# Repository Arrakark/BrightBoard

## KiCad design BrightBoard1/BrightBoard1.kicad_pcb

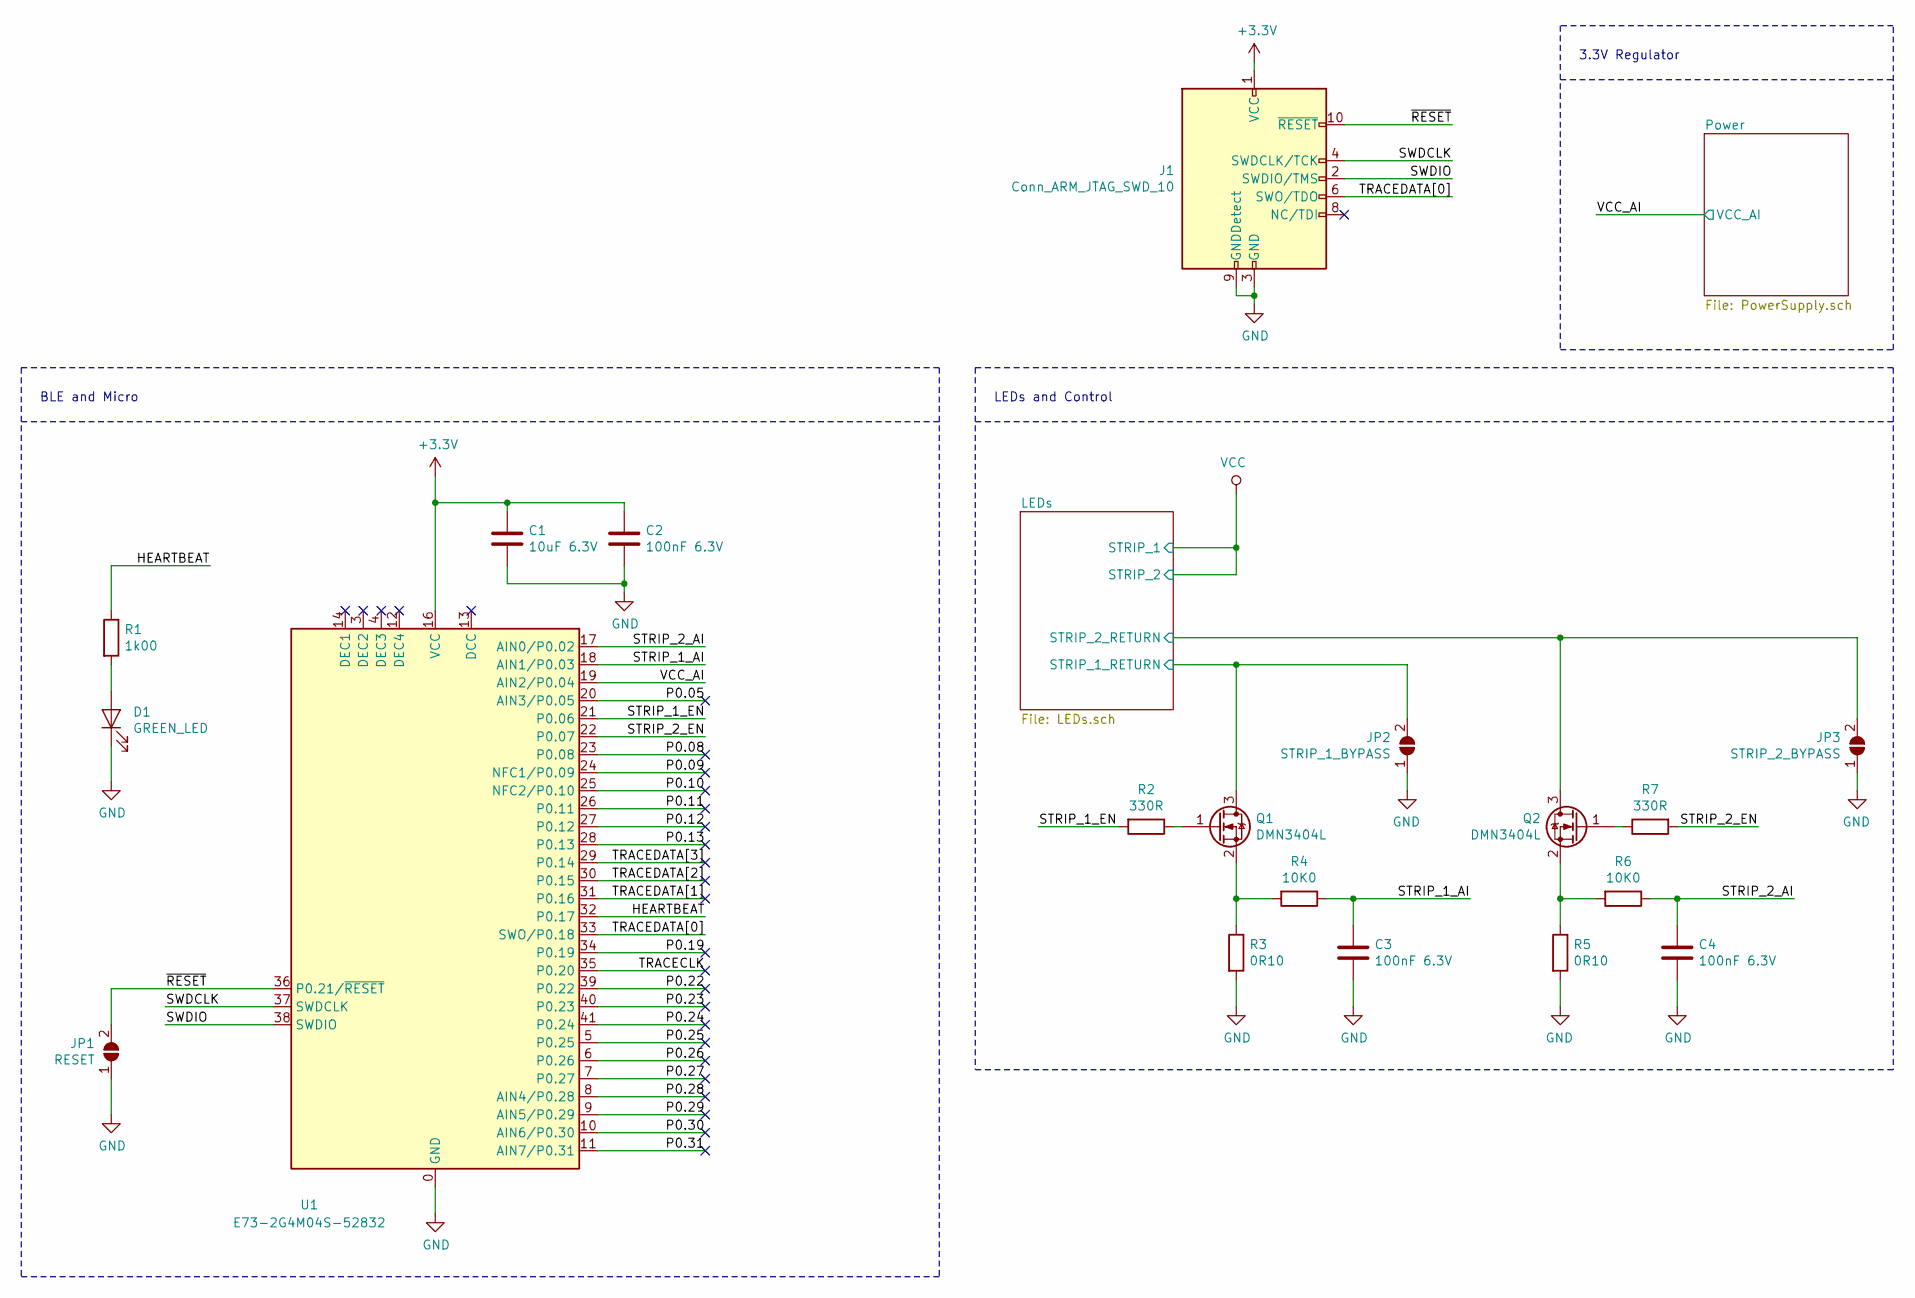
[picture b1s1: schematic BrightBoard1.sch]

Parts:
C1: 10uF 6.3V; C_0805_2012Metric_Pad1.15x1.40mm_HandSolder
C2, C3, C4: 100nF 6.3V; C_0805_2012Metric_Pad1.15x1.40mm_HandSolder
D1: GREEN_LED; LED_0805_2012Metric_Pad1.15x1.40mm_HandSolder
J1: Conn_ARM_JTAG_SWD_10; PinHeader_2x05_P1.27mm_Vertical_SMD
JP1: RESET; SolderJumper-2_P1.3mm_Open_RoundedPad1.0x1.5mm
JP2: STRIP_1_BYPASS; SolderJumper-2_P1.3mm_Open_RoundedPad1.0x1.5mm
JP3: STRIP_2_BYPASS; SolderJumper-2_P1.3mm_Open_RoundedPad1.0x1.5mm
Q1, Q2: DMN3404L; SOT-23
R1: 1k00; R_0805_2012Metric_Pad1.15x1.40mm_HandSolder
R2, R7: 330R; R_0805_2012Metric_Pad1.15x1.40mm_HandSolder
R3, R5: 0R10; R_0805_2012Metric_Pad1.15x1.40mm_HandSolder
R4, R6: 10K0; R_0805_2012Metric_Pad1.15x1.40mm_HandSolder
U1: E73-2G4M04S-52832; E73-2G4M04S

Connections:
+3V3: C1.1, C2.1, J1.1 (VCC), U1.16 (VCC); also elsewhere on the board
/HEARTBEAT: R1.1, U1.32 (P0.17)
/LEDs/STRIP_1_RETURN: JP2.2 (B), Q1.3 (D); also elsewhere on the board
/LEDs/STRIP_2_RETURN: JP3.2 (B), Q2.3 (D); also elsewhere on the board
/P0.05: U1.20 (AIN3/P0.05)
/P0.08: U1.23 (P0.08)
/P0.09: U1.24 (NFC1/P0.09)
/P0.10: U1.25 (NFC2/P0.10)
/P0.11: U1.26 (P0.11)
/P0.12: U1.27 (P0.12)
/P0.13: U1.28 (P0.13)
/P0.19: U1.34 (P0.19)
/P0.22: U1.39 (P0.22)
/P0.23: U1.40 (P0.23)
/P0.24: U1.41 (P0.24)
/P0.25: U1.5 (P0.25)
/P0.26: U1.6 (P0.26)
/P0.27: U1.7 (P0.27)
/P0.28: U1.8 (AIN4/P0.28)
/P0.29: U1.9 (AIN5/P0.29)
/P0.30: U1.10 (AIN6/P0.30)
/P0.31: U1.11 (AIN7/P0.31)
/STRIP_1_AI: C3.1, R4.1, U1.18 (AIN1/P0.03)
/STRIP_1_EN: R2.2, U1.21 (P0.06)
/STRIP_2_AI: C4.1, R6.1, U1.17 (AIN0/P0.02)
/STRIP_2_EN: R7.2, U1.22 (P0.07)
/SWDCLK: J1.4 (SWDCLK/TCK), U1.37 (SWDCLK)
/SWDIO: J1.2 (SWDIO/TMS), U1.38 (SWDIO)
/TRACECLK: U1.35 (P0.20)
/TRACEDATA[0]: J1.6 (SWO/TDO), U1.33 (SWO/P0.18)
/TRACEDATA[1]: U1.31 (P0.16)
/TRACEDATA[2]: U1.30 (P0.15)
/TRACEDATA[3]: U1.29 (P0.14)
/VCC_AI: U1.19 (AIN2/P0.04); also elsewhere on the board
/~RESET: J1.10 (~RESET~), JP1.2 (B), U1.36 (P0.21/~RESET)
GND: C1.2, C2.2, C3.2, C4.2, D1.1 (K), J1.3 (GND), J1.5 (GND), J1.9 (GNDDetect), JP1.1 (A), JP2.1 (A), JP3.1 (A), R3.2, R5.2, U1.0 (GND), U1.1 (GND), U1.2 (GND), U1.15 (GND), U1.42 (GND), U1.43 (GND); also elsewhere on the board
unnamed: D1.2 (A), R1.2
unnamed: Q1.1 (G), R2.1
unnamed: Q1.2 (S), R3.1, R4.2
unnamed: Q2.1 (G), R7.1
unnamed: Q2.2 (S), R5.1, R6.2

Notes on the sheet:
LEDs and Control
3.3V Regulator
BLE and Micro

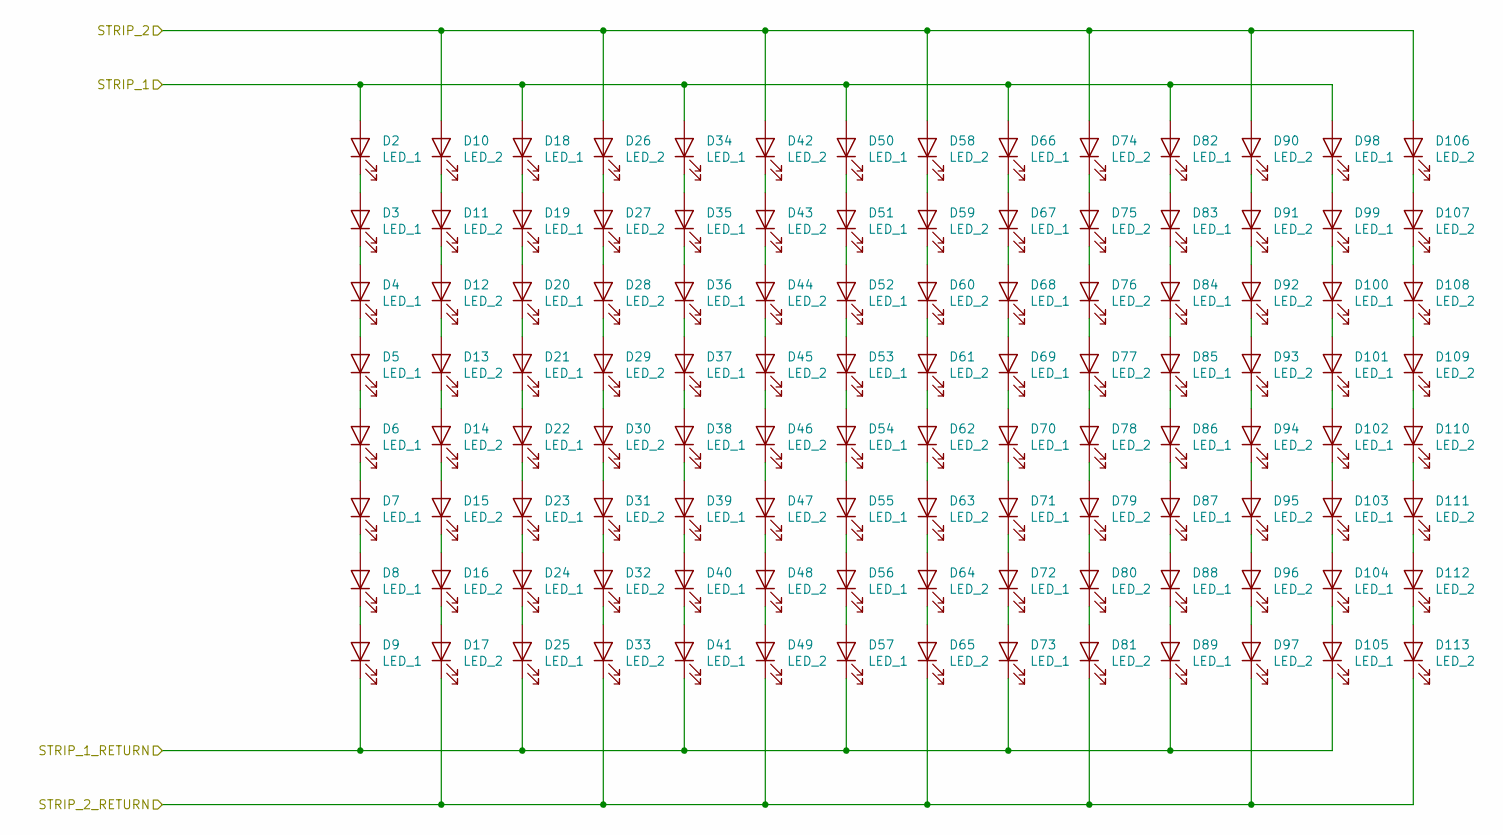
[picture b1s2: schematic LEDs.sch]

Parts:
D2, D3, D4, D5, D6, D7, D8, D9, D18, D19, D20, D21, D22, D23, D24, D25, D34, D35, D36, D37, D38, D39, D40, D41, D50, D51, D52, D53, D54, D55, D56, D57, D66, D67, D68, D69, D70, D71, D72, D73, D82, D83, D84, D85, D86, D87, D88, D89, D98, D99, D100, D101, D102, D103, D104, D105: LED_1; 2835_LED
D10, D11, D12, D13, D14, D15, D16, D17, D26, D27, D28, D29, D30, D31, D32, D33, D42, D43, D44, D45, D46, D47, D48, D49, D58, D59, D60, D61, D62, D63, D64, D65, D74, D75, D76, D77, D78, D79, D80, D81, D90, D91, D92, D93, D94, D95, D96, D97, D106, D107, D108, D109, D110, D111, D112, D113: LED_2; 2835_LED

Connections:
/LEDs/STRIP_1_RETURN: D9.1 (K), D25.1 (K), D41.1 (K), D57.1 (K), D73.1 (K), D89.1 (K), D105.1 (K); also elsewhere on the board
/LEDs/STRIP_2_RETURN: D17.1 (K), D33.1 (K), D49.1 (K), D65.1 (K), D81.1 (K), D97.1 (K), D113.1 (K); also elsewhere on the board
unnamed: D2.1 (K), D3.2 (A)
unnamed: D3.1 (K), D4.2 (A)
unnamed: D4.1 (K), D5.2 (A)
unnamed: D5.1 (K), D6.2 (A)
unnamed: D6.1 (K), D7.2 (A)
unnamed: D7.1 (K), D8.2 (A)
unnamed: D8.1 (K), D9.2 (A)
unnamed: D10.1 (K), D11.2 (A)
unnamed: D11.1 (K), D12.2 (A)
unnamed: D12.1 (K), D13.2 (A)
unnamed: D13.1 (K), D14.2 (A)
unnamed: D14.1 (K), D15.2 (A)
unnamed: D15.1 (K), D16.2 (A)
unnamed: D16.1 (K), D17.2 (A)
unnamed: D18.1 (K), D19.2 (A)
unnamed: D19.1 (K), D20.2 (A)
unnamed: D20.1 (K), D21.2 (A)
unnamed: D21.1 (K), D22.2 (A)
unnamed: D22.1 (K), D23.2 (A)
unnamed: D23.1 (K), D24.2 (A)
unnamed: D24.1 (K), D25.2 (A)
unnamed: D26.1 (K), D27.2 (A)
unnamed: D27.1 (K), D28.2 (A)
unnamed: D28.1 (K), D29.2 (A)
unnamed: D29.1 (K), D30.2 (A)
unnamed: D30.1 (K), D31.2 (A)
unnamed: D31.1 (K), D32.2 (A)
unnamed: D32.1 (K), D33.2 (A)
unnamed: D34.1 (K), D35.2 (A)
unnamed: D35.1 (K), D36.2 (A)
unnamed: D36.1 (K), D37.2 (A)
unnamed: D37.1 (K), D38.2 (A)
unnamed: D38.1 (K), D39.2 (A)
unnamed: D39.1 (K), D40.2 (A)
unnamed: D40.1 (K), D41.2 (A)
unnamed: D42.1 (K), D43.2 (A)
unnamed: D43.1 (K), D44.2 (A)
unnamed: D44.1 (K), D45.2 (A)
unnamed: D45.1 (K), D46.2 (A)
unnamed: D46.1 (K), D47.2 (A)
unnamed: D47.1 (K), D48.2 (A)
unnamed: D48.1 (K), D49.2 (A)
unnamed: D50.1 (K), D51.2 (A)
unnamed: D51.1 (K), D52.2 (A)
unnamed: D52.1 (K), D53.2 (A)
unnamed: D53.1 (K), D54.2 (A)
unnamed: D54.1 (K), D55.2 (A)
unnamed: D55.1 (K), D56.2 (A)
unnamed: D56.1 (K), D57.2 (A)
unnamed: D58.1 (K), D59.2 (A)
unnamed: D59.1 (K), D60.2 (A)
unnamed: D60.1 (K), D61.2 (A)
unnamed: D61.1 (K), D62.2 (A)
unnamed: D62.1 (K), D63.2 (A)
unnamed: D63.1 (K), D64.2 (A)
unnamed: D64.1 (K), D65.2 (A)
unnamed: D66.1 (K), D67.2 (A)
unnamed: D67.1 (K), D68.2 (A)
unnamed: D68.1 (K), D69.2 (A)
unnamed: D69.1 (K), D70.2 (A)
unnamed: D70.1 (K), D71.2 (A)
unnamed: D71.1 (K), D72.2 (A)
unnamed: D72.1 (K), D73.2 (A)
unnamed: D74.1 (K), D75.2 (A)
unnamed: D75.1 (K), D76.2 (A)
unnamed: D76.1 (K), D77.2 (A)
unnamed: D77.1 (K), D78.2 (A)
unnamed: D78.1 (K), D79.2 (A)
unnamed: D79.1 (K), D80.2 (A)
unnamed: D80.1 (K), D81.2 (A)
unnamed: D82.1 (K), D83.2 (A)
unnamed: D83.1 (K), D84.2 (A)
unnamed: D84.1 (K), D85.2 (A)
unnamed: D85.1 (K), D86.2 (A)
unnamed: D86.1 (K), D87.2 (A)
unnamed: D87.1 (K), D88.2 (A)
unnamed: D88.1 (K), D89.2 (A)
unnamed: D90.1 (K), D91.2 (A)
unnamed: D91.1 (K), D92.2 (A)
unnamed: D92.1 (K), D93.2 (A)
unnamed: D93.1 (K), D94.2 (A)
unnamed: D94.1 (K), D95.2 (A)
unnamed: D95.1 (K), D96.2 (A)
unnamed: D96.1 (K), D97.2 (A)
unnamed: D98.1 (K), D99.2 (A)
unnamed: D100.1 (K), D101.2 (A)
unnamed: D99.1 (K), D100.2 (A)
unnamed: D101.1 (K), D102.2 (A)
unnamed: D102.1 (K), D103.2 (A)
unnamed: D103.1 (K), D104.2 (A)
unnamed: D104.1 (K), D105.2 (A)
unnamed: D106.1 (K), D107.2 (A)
unnamed: D107.1 (K), D108.2 (A)
unnamed: D108.1 (K), D109.2 (A)
unnamed: D109.1 (K), D110.2 (A)
unnamed: D110.1 (K), D111.2 (A)
unnamed: D111.1 (K), D112.2 (A)
unnamed: D112.1 (K), D113.2 (A)
VCC: D2.2 (A), D10.2 (A), D18.2 (A), D26.2 (A), D34.2 (A), D42.2 (A), D50.2 (A), D58.2 (A), D66.2 (A), D74.2 (A), D82.2 (A), D90.2 (A), D98.2 (A), D106.2 (A); also elsewhere on the board

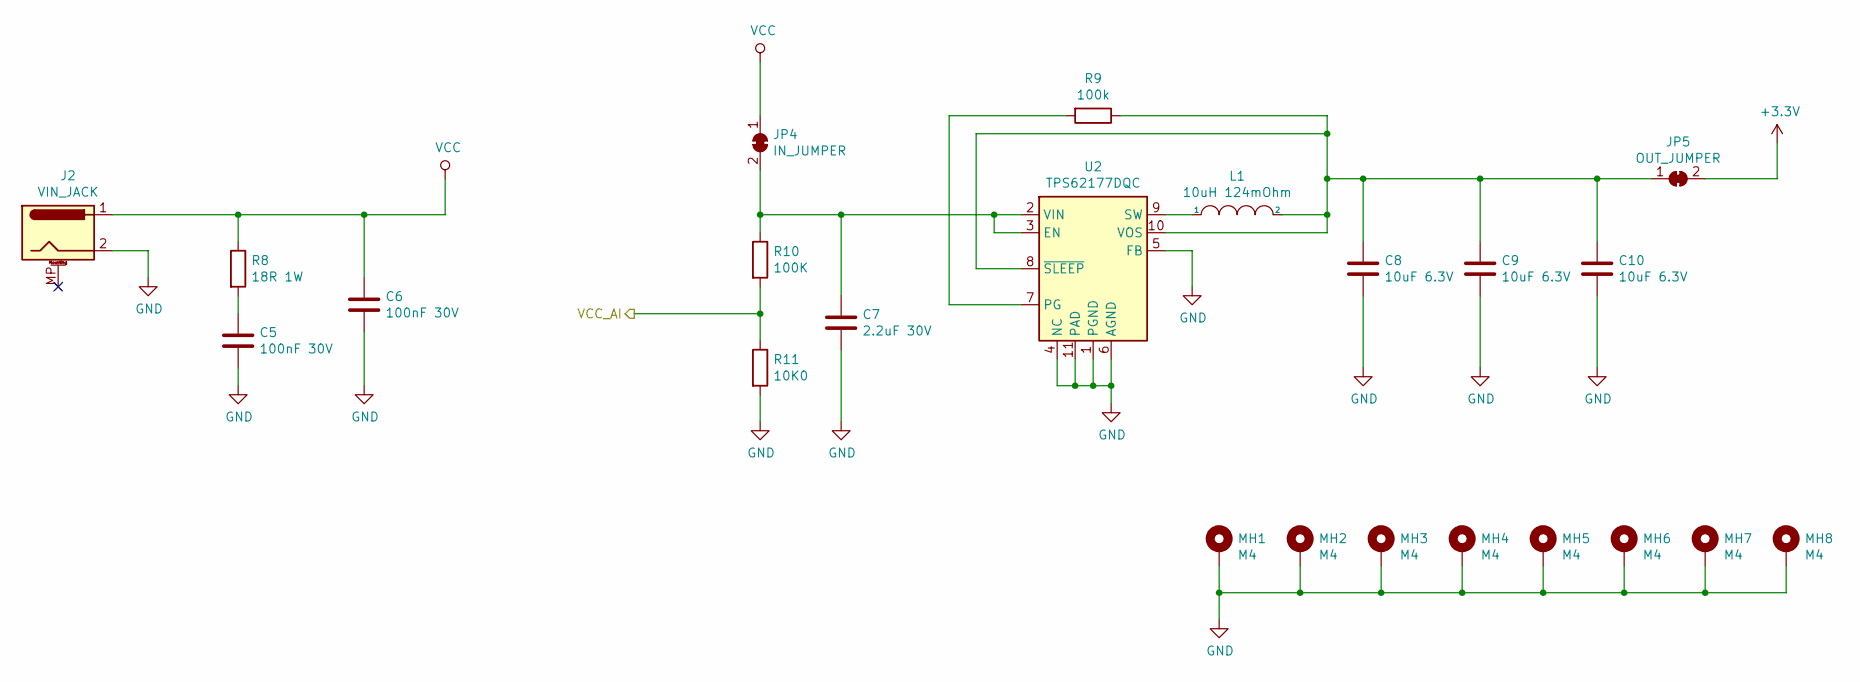
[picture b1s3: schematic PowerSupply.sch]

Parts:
C5, C6: 100nF 30V; C_0805_2012Metric_Pad1.15x1.40mm_HandSolder
C7: 2.2uF 30V; C_0805_2012Metric_Pad1.15x1.40mm_HandSolder
C8, C9, C10: 10uF 6.3V; C_0805_2012Metric_Pad1.15x1.40mm_HandSolder
J2: VIN_JACK; BarrelJack_CUI_PJ-102AH_Horizontal
JP4: IN_JUMPER; SolderJumper-2_P1.3mm_Bridged_RoundedPad1.0x1.5mm
JP5: OUT_JUMPER; SolderJumper-2_P1.3mm_Bridged_RoundedPad1.0x1.5mm
L1: 10uH 124mOhm; L_Taiyo-Yuden_NR-50xx_HandSoldering
MH1, MH2, MH3, MH4, MH5, MH6, MH7, MH8: M4; MountingHole_4.3mm_M4_ISO14580_Pad
R8: 18R 1W; R_2512_6332Metric_Pad1.52x3.35mm_HandSolder
R9: 100k; R_0805_2012Metric_Pad1.15x1.40mm_HandSolder
R10: 100K; R_0805_2012Metric_Pad1.15x1.40mm_HandSolder
R11: 10K0; R_0805_2012Metric_Pad1.15x1.40mm_HandSolder
U2: TPS62177DQC; WSON-10-1EP_2x3mm_P0.5mm_EP0.84x2.4mm_ThermalVias

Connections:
+3V3: JP5.2 (B); also elsewhere on the board
/VCC_AI: R10.2, R11.1; also elsewhere on the board
GND: C5.2, C6.2, C7.2, C8.2, C9.2, C10.2, J2.2, MH1.1, MH2.1, MH3.1, MH4.1, MH5.1, MH6.1, MH7.1, MH8.1, R11.2, U2.1 (PGND), U2.4 (NC), U2.5 (FB), U2.6 (AGND), U2.11 (PAD); also elsewhere on the board
unnamed: C5.1, R8.2
unnamed: C7.1, JP4.2 (B), R10.1, U2.2 (VIN), U2.3 (EN)
unnamed: C8.1, C9.1, C10.1, JP5.1 (A), L1.2, R9.1, U2.8 (~SLEEP), U2.10 (VOS)
unnamed: L1.1, U2.9 (SW)
unnamed: R9.2, U2.7 (PG)
VCC: C6.1, J2.1, JP4.1 (A), R8.1; also elsewhere on the board

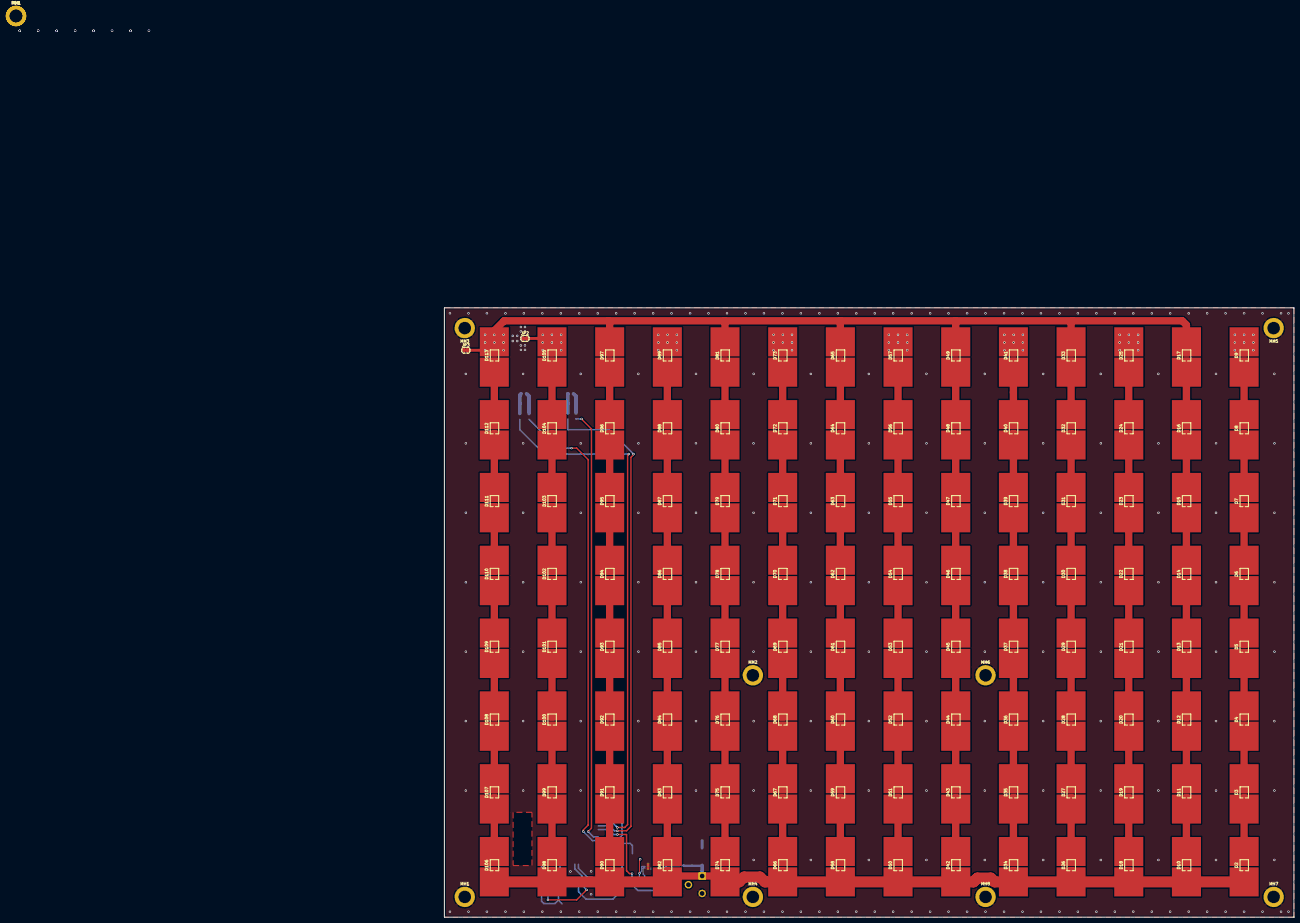
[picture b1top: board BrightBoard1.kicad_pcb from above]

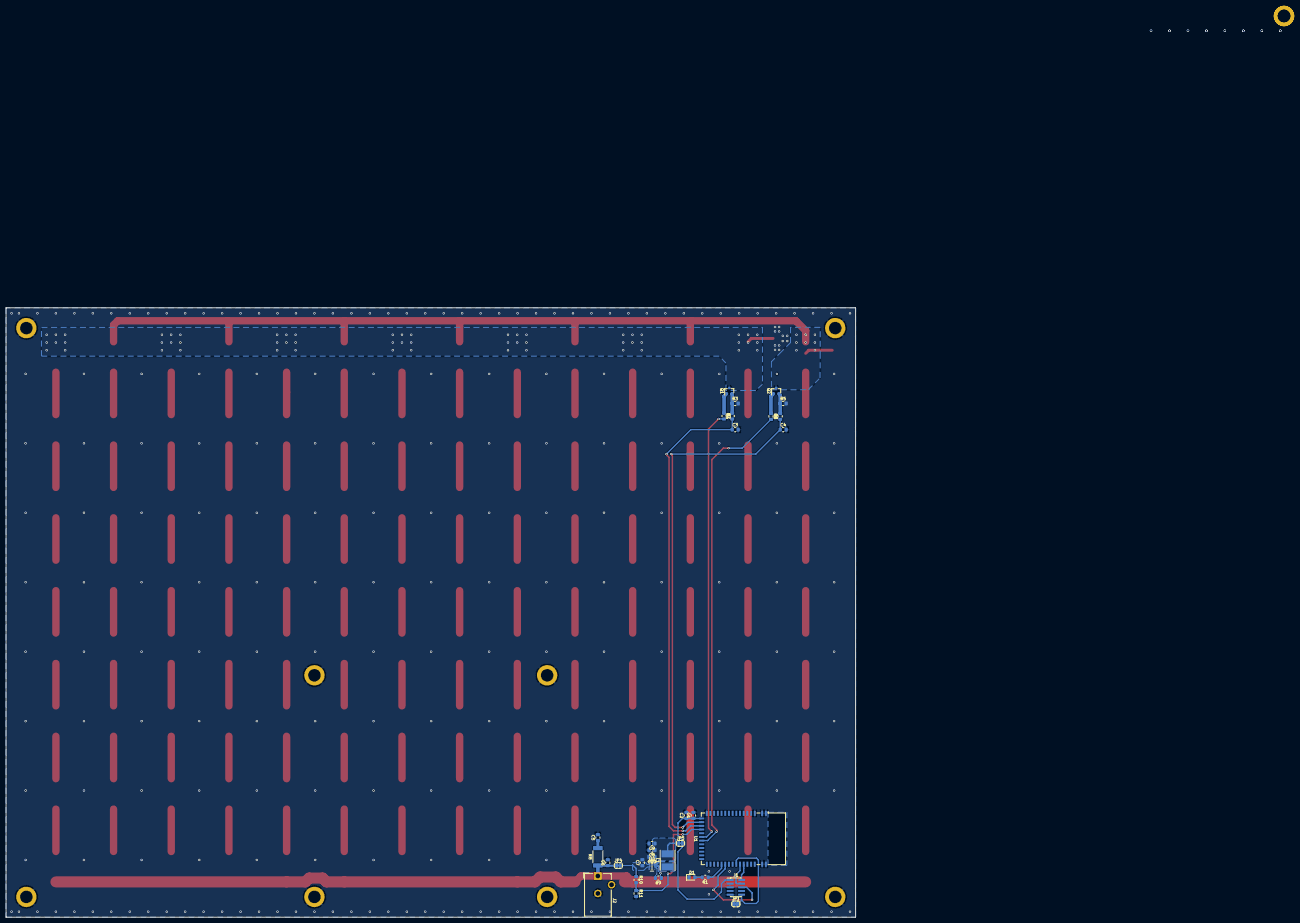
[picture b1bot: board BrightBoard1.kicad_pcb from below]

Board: 2 copper layers, 292.1 x 209.6 mm, 156 parts (32 on the bottom side), 123 nets.

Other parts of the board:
MH1#2, MH1#3: M4; MountingHole_4.3mm_M4_ISO14580_Pad

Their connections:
GND: MH1#3.1; also elsewhere on the board

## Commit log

2019-08-12 Init
2019-08-12 Renamed all LEDs
2019-08-12 Added mounting holes
2019-09-02 Layed out LEDs, 3.3v regulator; going to change it to a larger package
2019-09-08 Moving over?
2019-09-09 Routed all traces; need to finish ESD ring
2019-09-11 Finished
2019-09-26 Ready for first build
2019-09-27 Validated new prototype board
